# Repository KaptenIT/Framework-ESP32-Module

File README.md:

Based on the template in [FrameworkComputer/ExpansionCards](https://github.com/FrameworkComputer/ExpansionCards)

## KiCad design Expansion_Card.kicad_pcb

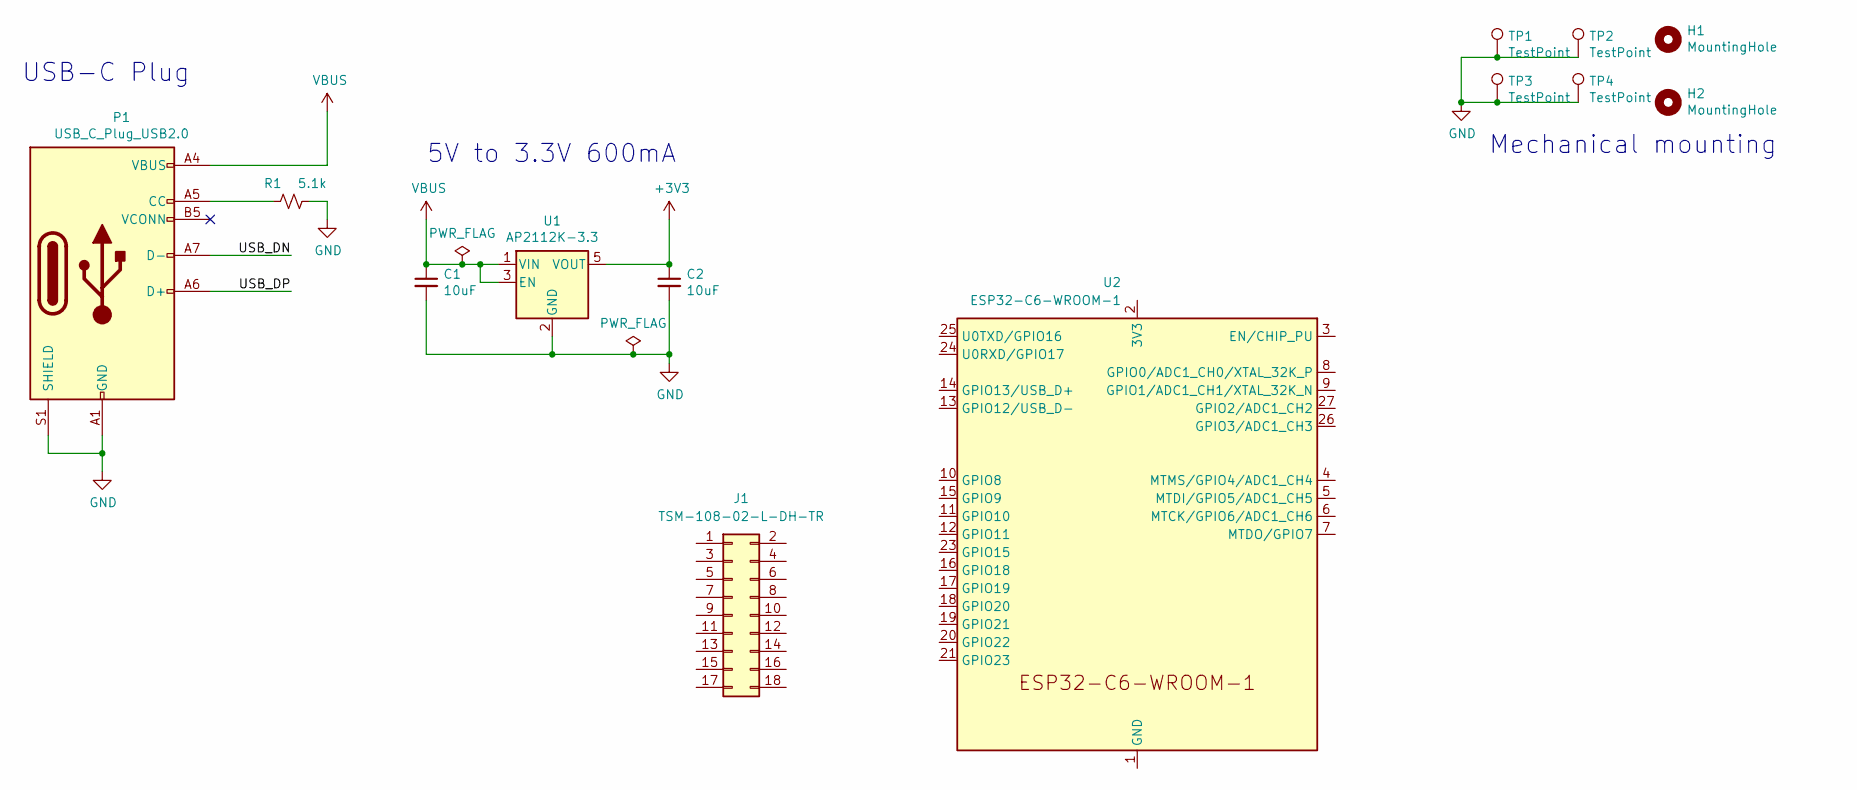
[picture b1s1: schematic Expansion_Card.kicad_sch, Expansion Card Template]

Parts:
C1, C2: 10uF; C_0805_2012Metric
H1, H2: MountingHole; MountingHole_2.2mm_M2
J1: TSM-108-02-L-DH-TR; PinHeader_2x09_P2.54mm_Vertical_SMD
P1: USB_C_Plug_USB2.0; USB_C_Plug_Molex_105444
R1: 5.1k; R_0603_1608Metric
TP1, TP2, TP3, TP4: TestPoint; TestPoint_Pad_1.5x1.5mm
U1: AP2112K-3.3; SOT-23-5
U2: ESP32-C6-WROOM-1

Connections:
+3V3: C2.1, U1.5 (VOUT)
/USB_DN: P1.A7 (D-)
/USB_DP: P1.A6 (D+)
GND: C1.2, C2.2, P1.A1 (GND), P1.A12 (GND), P1.B1 (GND), P1.B12 (GND), P1.S1 (SHIELD), R1.2, TP1.1, TP2.1, TP3.1, TP4.1, U1.2 (GND)
unnamed: P1.A5 (CC), R1.1
unnamed: U2.1 (GND), U2.28 (GND), U2.29 (GND)
VBUS: C1.1, P1.A4 (VBUS), P1.A9 (VBUS), P1.B4 (VBUS), P1.B9 (VBUS), U1.1 (VIN), U1.3 (EN)

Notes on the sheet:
5V to 3.3V 600mA
USB-C Plug
Mechanical mounting

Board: 2 copper layers, 13 parts (3 on the bottom side), 5 nets, no tracks yet.

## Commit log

2024-12-03 Add README.md
2024-12-03 Add project (early stages)
2024-12-03 Add 3d models

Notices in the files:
Expansion_Card.kicad_pcb:
This work is licensed under a Creative Commons Attribution 4.0 International License
